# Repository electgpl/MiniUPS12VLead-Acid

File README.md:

# Mini UPS 12V Lead-Acid | UVP Protector - Buck - Charger - Bypass

This project implements a **mini uninterruptible power supply (UPS)** designed for **12V Lead-Acid AGM/GEL batteries**.  
It integrates a dedicated **CN3767 lead-acid charger**, a **PMOS + Schottky bypass circuit**, a **TPS54360 buck regulator**, and an **undervoltage protection (UVP)** stage to ensure safe battery operation.  

The design focuses on maintaining stable 12V output while protecting the battery from undervoltage damage and ensuring correct charging cycles.  

---

## 🔑 Features

- **Battery chemistry supported:** 12V Lead-Acid (AGM, GEL).  
- **CN3767-based lead-acid charger** with constant-current/constant-voltage (CC/CV) charging.  
- **Bypass system:**  
  - PMOS + Schottky switch circuit.  
  - During charging, disconnects the battery from the load to allow proper charging.  
  - The load is powered instead by a regulated buck supply.  
- **Buck regulator stage:**  
  - Based on **TPS54360** DC/DC converter.  
  - Configured to **13.8V output** for stable system powering during battery charge.  
- **Undervoltage protection (UVP):**  
  - Implemented with **LM393 comparator** and **TL431 reference**.  
  - Controls a **back-to-back PMOS switch**.  
  - Cuts off the battery when voltage falls below **11V**.  
  - Latch-off behavior: system remains disconnected until external power is restored.  
- **2-layer PCB**, designed for compact size, thermal management, and robust operation.  

---

## 📂 Repository structure

- **/schematic/** → Circuit schematic files.  
- **/pcb/** → PCB layout files ready for fabrication.  
- **/doc/** → Technical notes and design explanation.  
- **/img/** → PCB renders and prototype photos.  

---

## 🔧 Typical applications

- DIY 12V backup supply for small systems.  
- Router, modem, or IoT device UPS.  
- Low-power embedded controllers requiring uninterrupted 12V operation.  
- Safe battery-powered test benches.  

---

## 📑 References

- [CN3767 Datasheet (Consonance)](http://www.consonance-elec.com/pdf/datasheet/DSE-CN3767.pdf)  
- [TPS54360 Datasheet (Texas Instruments)](https://www.ti.com/lit/ds/symlink/tps54360.pdf)  
- [LM393 Datasheet (Texas Instruments)](https://www.ti.com/lit/ds/symlink/lm393.pdf)  
- [TL431 Reference Datasheet (Texas Instruments)](https://www.ti.com/lit/ds/symlink/tl431.pdf)  

---

## 📸 Project preview

*(Insert here PCB renders and/or real prototype images)*  

---

## ⚖️ License

This project is released under the **MIT License**.  
You are free to use, modify, and distribute it, provided that proper credit is given.  

---

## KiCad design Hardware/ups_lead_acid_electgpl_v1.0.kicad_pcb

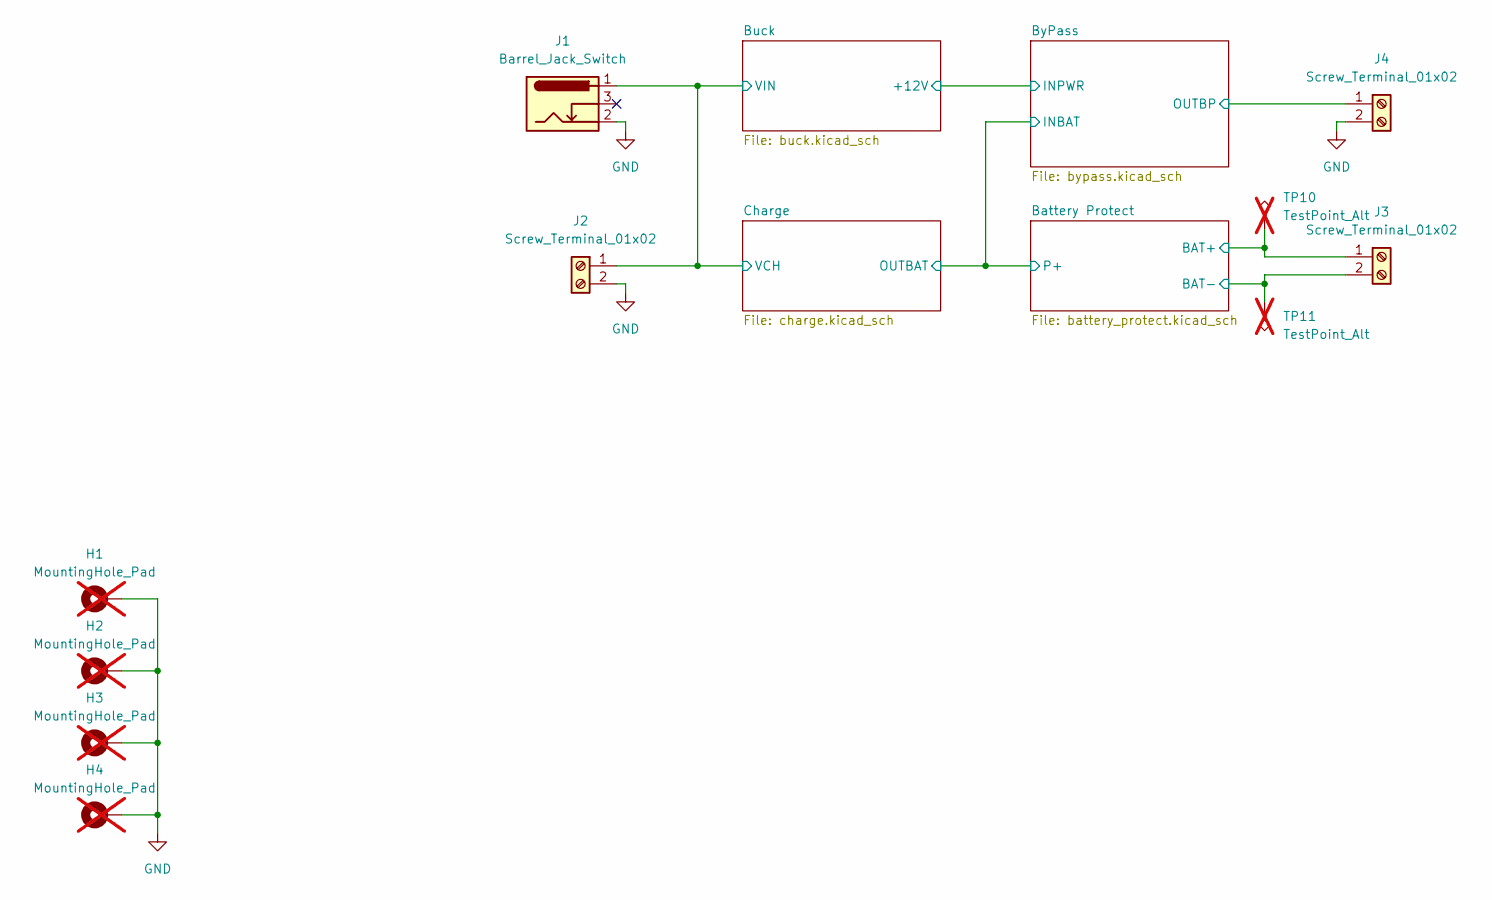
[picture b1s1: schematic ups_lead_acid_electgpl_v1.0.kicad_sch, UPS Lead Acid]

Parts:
H1, H2, H3, H4: MountingHole_Pad; MountingHole_3.2mm_M3_Pad_Via; not fitted
J1: Barrel_Jack_Switch; BarrelJack_GCT_DCJ200-10-A_Horizontal; MFR P/N DC-470-2.1GP; LCSC C194407
J2, J3, J4: Screw_Terminal_01x02; TerminalBlock_RND_205-00232_1x02_P5.08mm_Horizontal; MFR P/N WJ500V-5.08-2P; LCSC C8465
TP10, TP11: TestPoint_Alt; TestPoint_Bridge_Pitch5.08mm_Drill1.3mm; not fitted

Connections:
/Battery Protect/BAT+: J3.1, TP10.1; also elsewhere on the board
/Buck/VIN: J1.1, J2.1; also elsewhere on the board
/ByPass/OUTBP: J4.1; also elsewhere on the board
GND: H1.1, H2.1, H3.1, H4.1, J1.2, J2.2, J3.2, J4.2, TP11.1; also elsewhere on the board

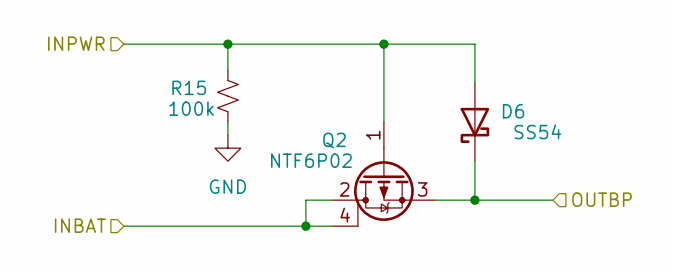
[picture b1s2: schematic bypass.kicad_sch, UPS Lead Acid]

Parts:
D6: SS54; D_SMC; MFR P/N SS54; LCSC C5199108
Q2: NTF6P02; SOT-223-3_TabPin2; MFR P/N NTF6P02T3G-VB; LCSC Part C154901
R15: 100k; R_0603_1608Metric; MFR P/N FRC0603J104 TS; LCSC Part C99198

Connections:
+12V: D6.2 (A), Q2.1 (G), R15.2; also elsewhere on the board
/Battery Protect/P+: Q2.2 (D), Q2.4 (D); also elsewhere on the board
/ByPass/OUTBP: D6.1 (K), Q2.3 (S); also elsewhere on the board
GND: R15.1; also elsewhere on the board

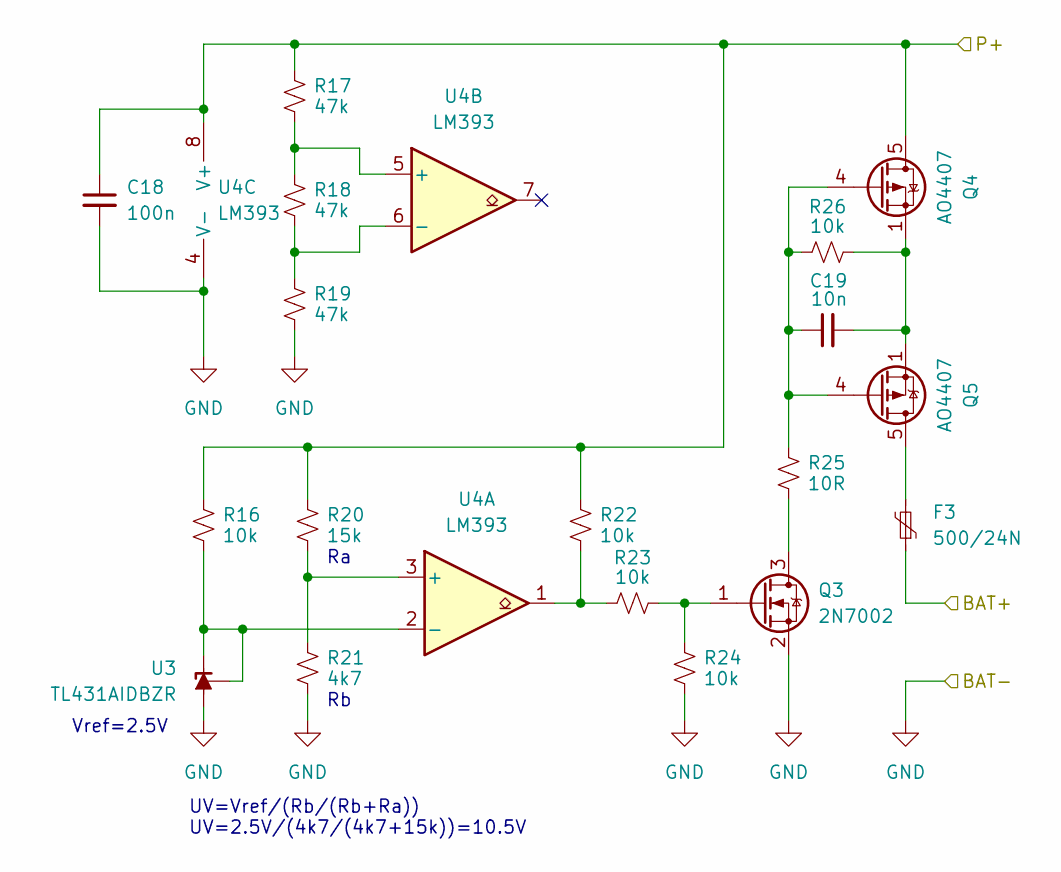
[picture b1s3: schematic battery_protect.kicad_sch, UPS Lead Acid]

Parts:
C18: 100n; C_0603_1608Metric; MFR P/N CL10B104KB8NNNC; LCSC C1591
C19: 10n; C_0603_1608Metric; MFR P/N CL10B103KB8NNNC; LCSC C1589
F3: 500/24N; Fuse_2920_7451Metric; MFR P/N SMD2920-500/24N; LCSC C6165172
Q3: 2N7002; SOT-23; MFR P/N 2N7002,215; LCSC C65189
Q4, Q5: AO4407; SOP-8_3.9x4.9mm_P1.27mm; MFR P/N AO4407A; LCSC C2841482
R16, R22, R23, R24, R26: 10k; R_0603_1608Metric; MFR P/N FRC0603J103 TS; LCSC C2930027
R17, R18, R19: 47k; R_0603_1608Metric; MFR P/N FRC0603F4702TS; LCSC C2907042
R20: 15k; R_0603_1608Metric; MFR P/N FRC0603F1502TS; LCSC C2906995
R21: 4k7; R_0603_1608Metric; MFR P/N FRC0603J472 TS; LCSC C2907166
R25: 10R; R_0603_1608Metric; MFR P/N FRC0603J100 TS; LCSC C2907091
U3: TL431AIDBZR; SOT-23; MFR P/N TL431AIDBZR; LCSC C23892
U4: LM393; SOIC-8_3.9x4.9mm_P1.27mm; MFR P/N LM393DR; LCSC C67470

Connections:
/Battery Protect/BAT+: F3.1; also elsewhere on the board
/Battery Protect/P+: C18.1, Q4.5 (D), Q4.6 (D), Q4.7 (D), Q4.8 (D), R16.1, R17.1, R20.1, R22.1, U4.8 (V+); also elsewhere on the board
GND: C18.2, Q3.2 (S), R19.2, R21.2, R24.2, U3.3 (A), U4.4 (V-); also elsewhere on the board
unnamed: C19.2, Q4.1 (S), Q4.2 (S), Q4.3 (S), Q5.1 (S), Q5.2 (S), Q5.3 (S), R26.2
unnamed: F3.2, Q5.5 (D), Q5.6 (D), Q5.7 (D), Q5.8 (D)
unnamed: Q3.3 (D), R25.2
unnamed: Q3.1 (G), R23.2, R24.1
unnamed: C19.1, Q4.4 (G), Q5.4 (G), R25.1, R26.1
unnamed: R22.2, R23.1, U4.1
unnamed: R16.2, U3.1 (K), U3.2 (REF), U4.2 (-)
unnamed: R20.2, R21.1, U4.3 (+)
unnamed: R17.2, R18.1, U4.5 (+)
unnamed: R18.2, R19.1, U4.6 (-)

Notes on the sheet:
UV=Vref/(Rb/(Rb+Ra)) UV=2.5V/(4k7/(4k7+15k))=10.5V
Vref=2.5V

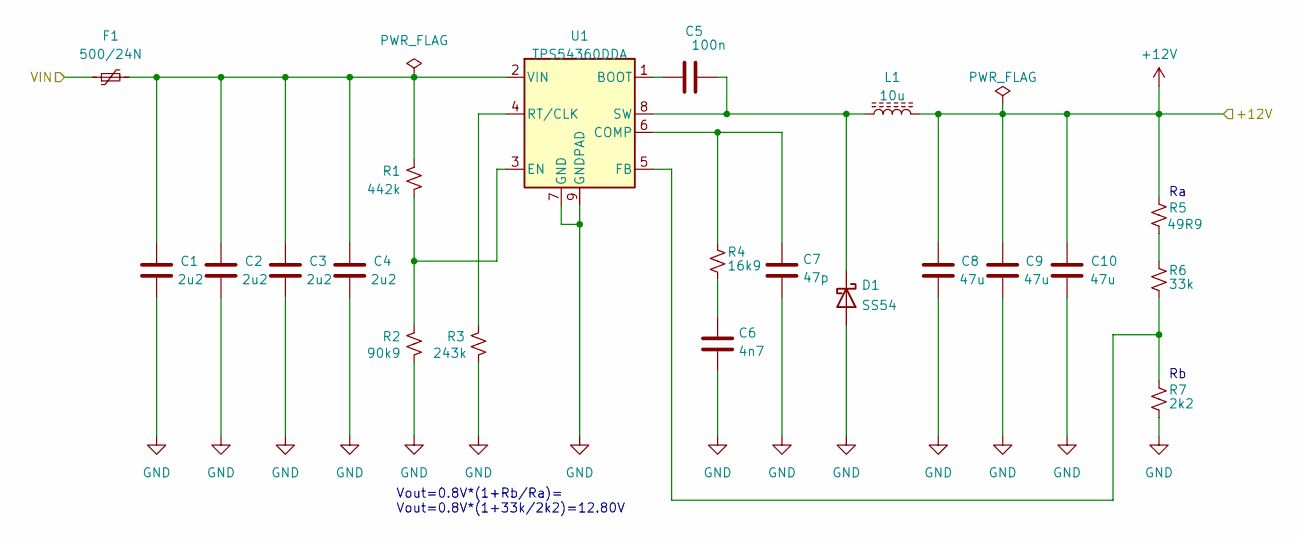
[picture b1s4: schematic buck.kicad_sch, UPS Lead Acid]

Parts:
C1, C2, C3, C4: 2u2; C_0603_1608Metric; MFR P/N CL10A225KB8NNNC; LCSC C913904
C5: 100n; C_0603_1608Metric; MFR P/N CL10B104KB8NNNC; LCSC C1591
C6: 4n7; C_0603_1608Metric; MFR P/N CL10B472KB8NNNC; LCSC C1621
C7: 47p; C_0603_1608Metric; MFR P/N CL10C470JB8NNNC; LCSC C1671
C8, C9, C10: 47u; C_0805_2012Metric; MFR P/N CL21A226MAYNNNE; LCSC C602037
D1: SS54; D_SMC; MFR P/N SS54; LCSC C5199108
F1: 500/24N; Fuse_2920_7451Metric; MFR P/N SMD2920-500/24N; LCSC C6165172
L1: 10u; L_Taiyo-Yuden_NR-60xx; MFR P/N VLS6045EX-100M; LCSC C360734
R1: 442k; R_0603_1608Metric; MFR P/N 0603WAF4423T5E; LCSC C23175
R2: 90k9; R_0603_1608Metric; MFR P/N FRC0603F9092TS; LCSC C2930136
R3: 243k; R_0603_1608Metric; MFR P/N FRC0603F2433TS; LCSC C7467321
R4: 16k9; R_0603_1608Metric; MFR P/N FRC0603F1692TS; LCSC C2933158
R5: 49R9; R_0603_1608Metric; MFR P/N FRC0603F49R9TS; LCSC C2930110
R6: 33k; R_0603_1608Metric; MFR P/N FRC0603J333 TS; LCSC C2907153
R7: 2k2; R_0603_1608Metric; MFR P/N FRC0603J222 TS; LCSC C2907117
U1: TPS54360DDA; HSOP-8-1EP_3.9x4.9mm_P1.27mm_EP2.41x3.1mm_ThermalVias; MFR P/N TPS54360DDAR; LCSC C44377

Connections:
+12V: C8.2, C9.2, C10.2, L1.2, R5.1; also elsewhere on the board
/Buck/VIN: F1.1; also elsewhere on the board
GND: C1.1, C2.1, C3.1, C4.1, C6.2, C7.2, C8.1, C9.1, C10.1, D1.2 (A), R2.2, R3.2, R7.2, U1.7 (GND), U1.9 (GNDPAD); also elsewhere on the board
unnamed: C6.1, R4.2
unnamed: C5.2, D1.1 (K), L1.1, U1.8 (SW)
unnamed: R5.2, R6.1
unnamed: C5.1, U1.1 (BOOT)
unnamed: C7.1, R4.1, U1.6 (COMP)
unnamed: R1.2, R2.1, U1.3 (EN)
unnamed: R6.2, R7.1, U1.5 (FB)
unnamed: R3.1, U1.4 (RT/CLK)
unnamed: C1.2, C2.2, C3.2, C4.2, F1.2, R1.1, U1.2 (VIN)

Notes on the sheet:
Vout=0.8V*(1+Rb/Ra)= Vout=0.8V*(1+33k/2k2)=12.80V

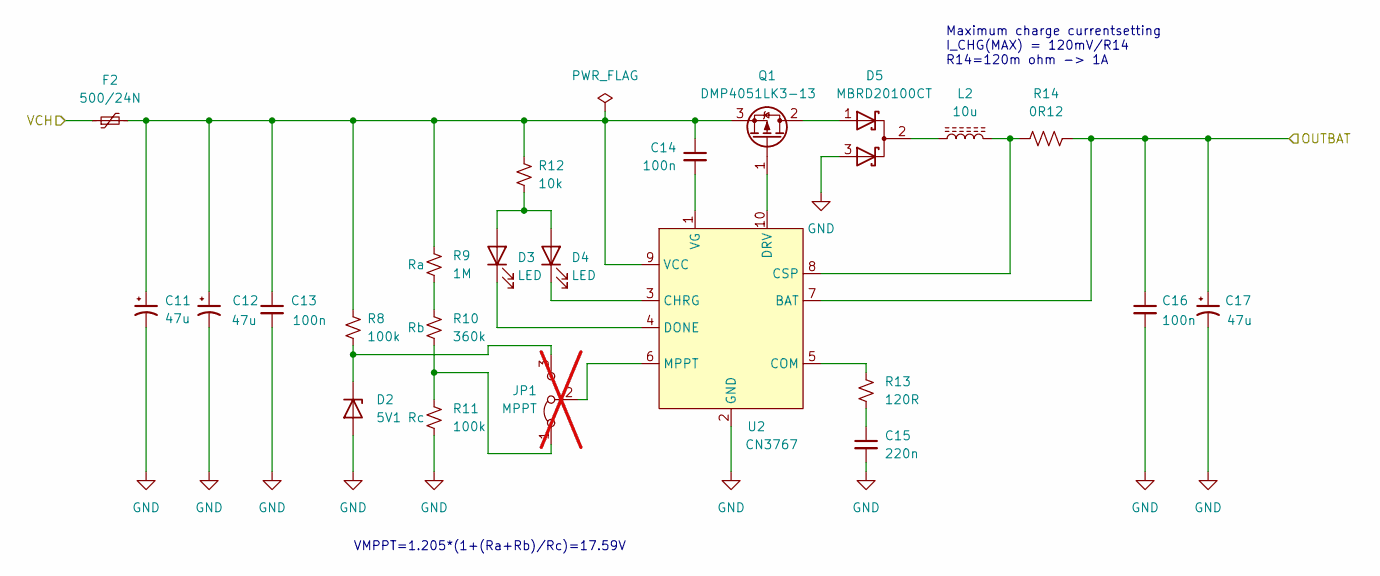
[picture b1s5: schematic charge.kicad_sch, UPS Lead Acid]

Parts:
C11, C12, C17: 47u; C_0805_2012Metric; MFR P/N CL21A226MAYNNNE; LCSC C602037
C13, C14, C16: 100n; C_0603_1608Metric; MFR P/N CL10B104KB8NNNC; LCSC C1591
C15: 220n; C_0603_1608Metric; MFR P/N CL10B224KB8NNNC; LCSC C64705
D2: 5V1; D_SOD-123; MFR P/N MMSZ5231BT1G; LCSC C66198
D3, D4: LED; LED_0603_1608Metric; MFR P/N XL-1608UYC-06; LCSC C965802
D5: MBRD20100CT; TO-252-2; MFR P/N MBRD20100CT-13; LCSC C460890
F2: 500/24N; Fuse_2920_7451Metric; MFR P/N SMD2920-500/24N; LCSC C6165172
JP1: MPPT; SolderJumper-3_P1.3mm_Open_Pad1.0x1.5mm; not fitted
L2: 10u; L_Taiyo-Yuden_NR-60xx; MFR P/N VLS6045EX-100M; LCSC C360734
Q1: DMP4051LK3-13; TO-252-2; MFR P/N DMP4051LK3-13; LCSC C397952
R8, R11: 100k; R_0603_1608Metric; MFR P/N FRC0603J104 TS; LCSC C2907088
R9: 1M; R_0603_1608Metric; MFR P/N FRC0603F1004TS; LCSC C2907003
R10: 360k; R_0603_1608Metric; MFR P/N FRC0603F3603TS; LCSC C2907029
R12: 10k; R_0603_1608Metric; MFR P/N FRC0603J103 TS; LCSC C2930027
R13: 120R; R_0603_1608Metric; MFR P/N FRC0603J121 TS; LCSC C2907096
R14: 0R12; R_2512_6332Metric; MFR P/N PT2512FK-7W0R12L; LCSC C875871
U2: CN3767; SSOP-10_3.9x4.9mm_P1.00mm; MFR P/N CN3767; LCSC C81968

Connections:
/Battery Protect/P+: C16.1, C17.1, R14.2, U2.7 (BAT); also elsewhere on the board
/Buck/VIN: F2.1; also elsewhere on the board
GND: C11.2, C12.2, C13.2, C15.2, C16.2, C17.2, D2.2 (A), D5.3 (A), R11.2, U2.2 (GND); also elsewhere on the board
unnamed: C15.1, R13.2
unnamed: D2.1 (K), JP1.3 (B), R8.2
unnamed: D3.2 (A), D4.2 (A), R12.2
unnamed: D3.1 (K), U2.4 (DONE)
unnamed: D4.1 (K), U2.3 (CHRG)
unnamed: D5.2 (K), L2.1
unnamed: JP1.1 (A), R10.2, R11.1
unnamed: JP1.2 (C), U2.6 (MPPT)
unnamed: D5.1 (A), Q1.2 (D)
unnamed: Q1.1 (G), U2.10 (DRV)
unnamed: C11.1, C12.1, C13.1, C14.1, F2.2, Q1.3 (S), R8.1, R9.1, R12.1, U2.9 (VCC)
unnamed: R9.2, R10.1
unnamed: R13.1, U2.5 (COM)
unnamed: L2.2, R14.1, U2.8 (CSP)
unnamed: C14.2, U2.1 (VG)

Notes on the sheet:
VMPPT=1.205*(1+(Ra+Rb)/Rc)=17.59V
Maximum charge currentsetting I_CHG(MAX) = 120mV/R14 R14=120m ohm -> 1A

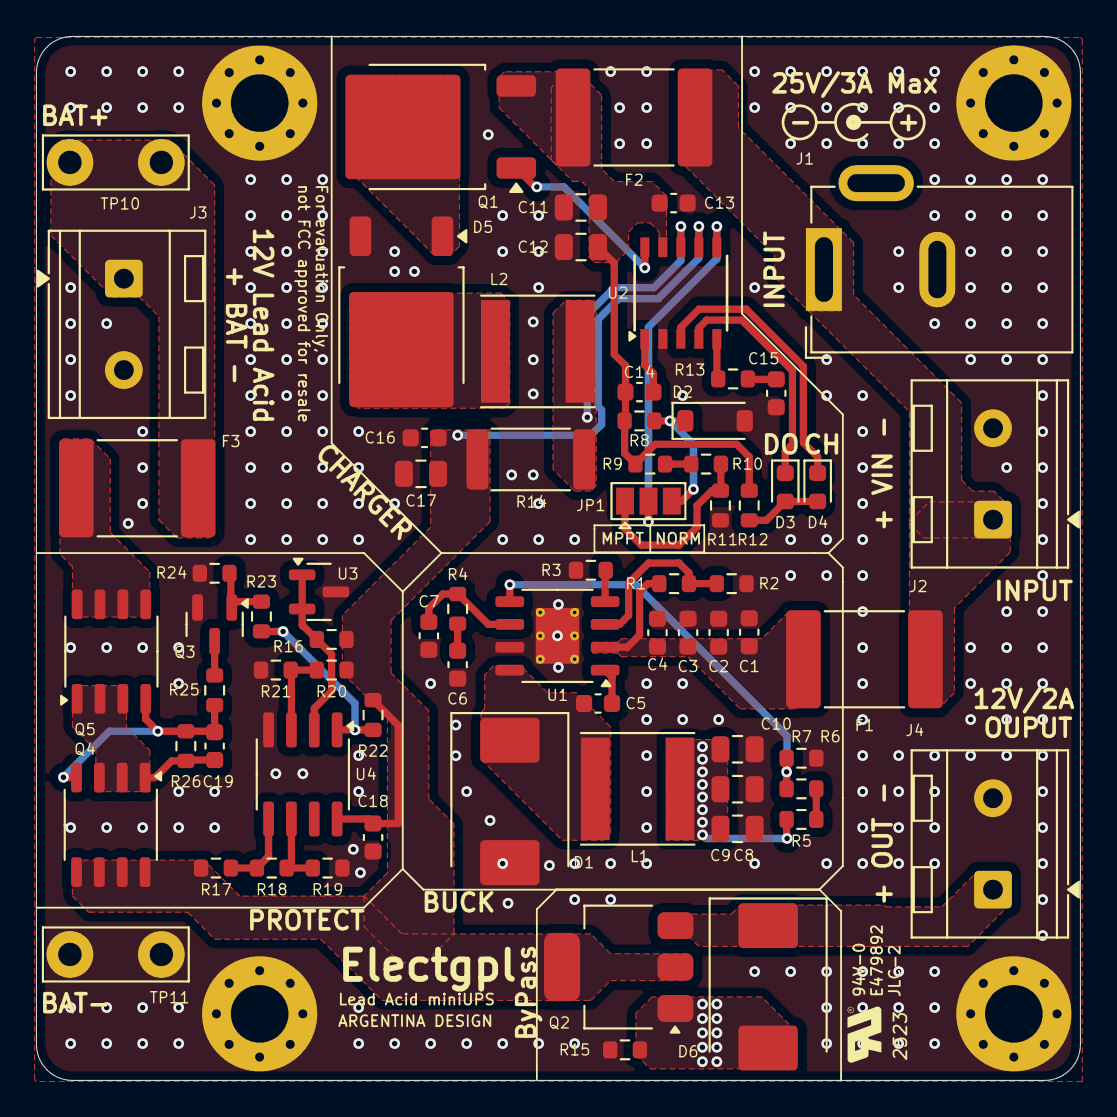
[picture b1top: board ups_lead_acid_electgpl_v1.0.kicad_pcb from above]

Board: 2 copper layers, 58.0 x 58.0 mm, 76 parts (0 on the bottom side), 40 nets.

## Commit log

2025-08-25 add zip kicad files
